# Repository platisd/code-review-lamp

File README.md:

# Code Review Lamp
A colorful lamp to notify the developer team for pending code reviews.

## What?
Code Review Lamp is a Neopixel-based, WiFi-enabled gadget that reminds developers to peer-review their colleagues' code. For each submission that has not been reviewed enough, it dims up and down at a color that is specific to the developer who is trying to introduce a new functionality to a project. The lamp stops shining once the code has either received enough reviews by the team, been merged or designated as *Work In Progress*. Currently, it is configured to work with [Gerrit](https://www.gerritcodereview.com/) (v.2.15) or GitHub, but it could be programmed to fetch data from different tools such as Jenkins, GitLab etc.

The gadget is comprised of an [ESP8266 microcontroller module](https://wiki.wemos.cc/products:d1:d1_mini) that connects wirelessly to the internet, as well as a [Neopixel ring](https://www.adafruit.com/product/1463) which displays various colors.

## Why?
At work, we are a fast-paced team that likes to commit (relatively) small and often. Every commit does not only have to pass the various tests that are being run by our Continuous Integration machinery, but also gets extensively code reviewed before allowed to be merged. Since we are *six* in total and our internal code of conduct dictates *two* positive approvals for each new submission, the lack of responsiveness when it comes to reviewing, can impede the development process and speed.

In an ideal world, developers would check their notification emails and would proceed on with reviewing their peer's code. However, as they are too absorbed by their ongoing work and perhaps slightly overwhelmed by the amount of emails they receive, these emails tend to be ignored. The common thought is that someone else in the team is going to review the code, but often no one does.

We have employed two different techniques so far to solve the problem. The first one includes shouting **CODE REVIEW** loudly and the second placing color-coded bean bags (I am not kidding :laughing:) on each others' desks. The third that hopes to rule them all is the Code Review Lamp!

Its advantage is that it continuously, and discretely, reminds developers that **the team** needs to review code and thus someone's work is being blocked as long as the lamp is shining. Additionally, they can see who is requesting the code review and how many reviews need to be conducted.

## How?
Reaping the benefits of the Code Review Lamp is simple for the development team member. They merely need to push code to Gerrit, add the group which includes all team members to the review and set the review to *Work in Progress* or *Ready for review* depending on whether they want the team to start or stop reviewing the code.

We have included a special user in our team's Gerrit group, representing the lamp, which is added along the team to each review. This user is being utilized by an ESP8266 microcontroller which connects to WiFi and [queries](https://gerrit-review.googlesource.com/Documentation/rest-api-changes.html) Gerrit for open reviews where this "lamp user" is a reviewer. Of course, it is not necessary to have a separate user for the lamp. Any team member's already existing account can be used and this way Code Review Lamps can be personalized. However, since we consider code reviews a *team activity* and the foundation of cross-functionality and knowledge-sharing, we have opted for the "team approach".

Next, for each review the user is assigned to, we determine how many reviews have been conducted and if they fall short of our agreed threshold, a color that corresponds to the *owner* of the review is displayed on the Neopixel ring.

### Software
The [Gerrit firmware](https://github.com/platisd/code-review-lamp/blob/master/firmware/gerrit_watcher/gerrit_watcher.ino), compatible with ESP8266 microcontrollers, utilizes the [Adafruit Neopixel](https://github.com/adafruit/Adafruit_NeoPixel) library to control the Neopixel ring. When using **Gerrit**, the JSON response is parsed manually, as existing solutions which would nicely serialize the whole stream would frequently cause heap overflow.

The [GitHub firmware](https://github.com/platisd/code-review-lamp/blob/master/firmware/github_watcher/github_watcher.ino) on the other hand does not parse the JSON response coming from **GitHub** itself directly. This is due to the API response being overly verbose for the ESP8266 microcontroller, which renders parsing it on the microcontroller infeasible. Instead, an external server has to be used which will process the data and merely send what colors should be displayed. An example of such a server, written in Python3, can be found [here](https://github.com/platisd/code-review-lamp/blob/master/firmware/github_watcher/github_reviews_watcher.py).

### Hardware
The gadget is rather simple to source and assemble. The only "custom" part is the [PCB](https://github.com/platisd/code-review-lamp/tree/master/hardware/gerrit_lamp) which merely connects the ESP8266 module with the Neopixel ring.

### Get started
After you have assembled the hardware, flash the firmware by following the steps below:
* If on Windows or Mac, download the [Serial to USB chip drivers](https://wiki.wemos.cc/downloads)
* Download and install the latest [Arduino IDE](https://www.arduino.cc/en/Main/Software) for your distribution
* Install the `Adafruit Neopixel` library
  * In Arduino IDE, click on `Sketch` :arrow_right: `Include Library` :arrow_right: `Manage Libraries`
  * Look for `Adafruit NeoPixel` and install the `Adafruit NeoPixel by adafruit`
* Install the ESP8266 SDK
  * In Arduino IDE, click on `File` :arrow_right: `Preferences` :arrow_right: `Additional Board Manager URLs`
  * Paste `http://arduino.esp8266.com/stable/package_esp8266com_index.json` and click `OK`
  * In Arduino IDE, click on `Tools` :arrow_right: `Board` :arrow_right: `Boards Manager`
  * Look for `esp8266` and install the `esp8266 by ESP8266 Community`
* Select the Wemos D1 Mini board
  * In Arduino IDE, click on `Tools` :arrow_right: `Board` :arrow_right: `LOLIN(WEMOS) D1 R2 & mini`
* Select the serial port your Code Review Lamp is connected to
  * In Arduino IDE, click on `Tools` :arrow_right: `Port`
* Copy & paste the [code](https://github.com/platisd/code-review-lamp/blob/master/firmware/gerrit_watcher/gerrit_watcher.ino) to your IDE
* Make the necessary adjustments for your own SSID, username etc
  * GitHub Token
    * Create a [personal access token](https://github.com/settings/tokens)
    * Give it all `repo` permissions if you want it to access your private repositories too, otherwise just `public_repo`
* Upload the firmware by clicking `Upload` (the right arrow button on the upper left corner of your IDE)

### How to use
* Commit your change to Gerrit or GitHub
* Add the group which includes the team as reviewers
  * A special "notification" user that will trigger the lamp should be part of the group
* ???
* Get your code reviewed faster!

## Components
* [Code Review Lamp PCB](https://www.pcbway.com/project/shareproject/W17435BSW42_code_review_lamp.html)
* [3D printed case](https://www.tinkercad.com/things/evNud1d8GYI)
* [16 RGB LED Neopixel Ring](https://www.adafruit.com/product/1463)
* [Wemos D1 Mini](https://wiki.wemos.cc/products:d1:d1_mini)
* 330Ohm resistor
* 470uF/16V capacitor
* M3x40mm screws (4)
* M3 nuts (4)
* Micro USB cable

## Media
* Article on [platis.solutions](https://platis.solutions/blog/2018/09/26/code-review-lamp/)
* [Demo video](https://www.youtube.com/watch?v=TPO2nQkfprY)

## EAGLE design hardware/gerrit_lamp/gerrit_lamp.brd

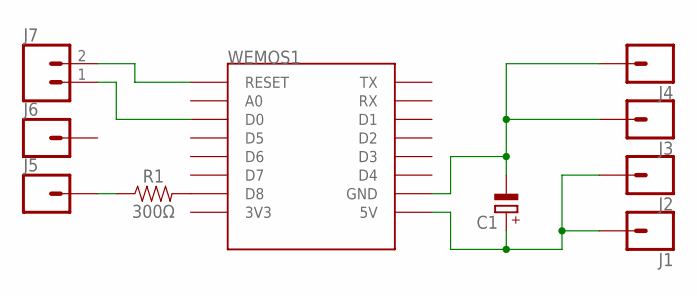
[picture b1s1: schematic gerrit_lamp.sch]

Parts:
C1: CPOL-EUE5-5; E5-5
J1, J2, J3, J4, J5, J6: CONN_01PTH_NO_SILK_KIT; 1X01NS_KIT
J7: CONN_02; 1X02
R1: 300Ω; AXIAL-0.3
WEMOS1: WEMOS-D1-MINI

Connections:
D0: J7.1, WEMOS1.D0
GND: C1.-, J3.1, J4.1, WEMOS1.GND
unnamed: R1.P$2 (2), WEMOS1.D8
unnamed: J5.1, R1.P$1 (1)
RST: J7.2, WEMOS1.RESET
VCC: C1.+, J1.1, J2.1, WEMOS1.5V

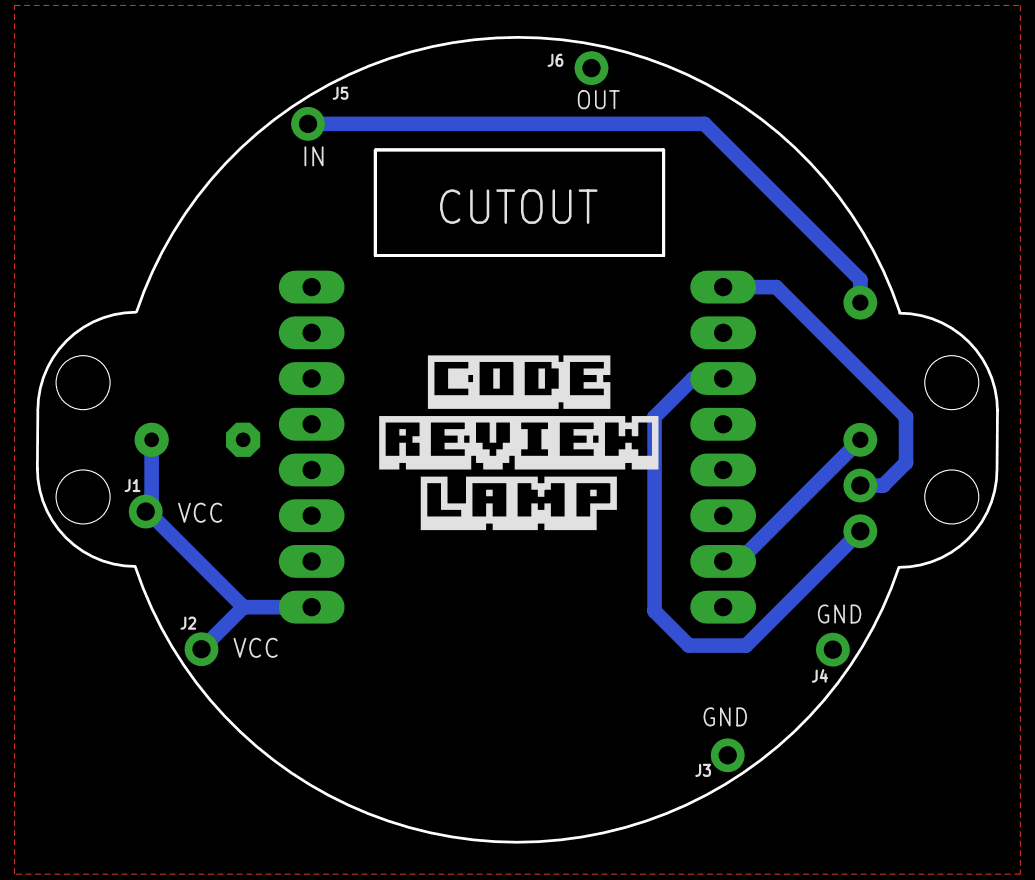
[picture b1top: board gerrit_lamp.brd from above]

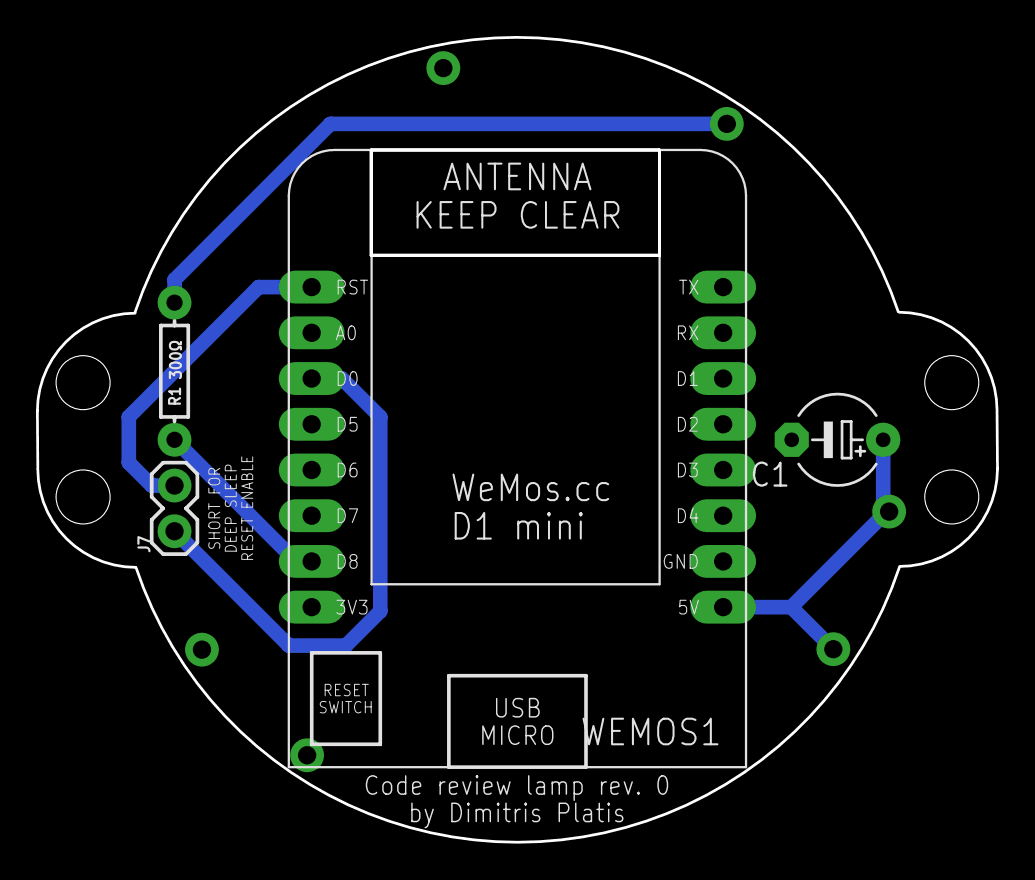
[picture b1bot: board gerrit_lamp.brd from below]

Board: 2 copper layers, 53.3 x 44.7 mm, 10 parts (4 on the bottom side), 6 nets.

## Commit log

2018-09-03 Add gitignore
2018-09-03 Add first version of gerrit watcher
2018-09-04 Use streams to parse JSON input
2018-09-04 Decrease heap memory usage
    Current setup has been tested with up to 7
    reviews. Serial is very shaky for some reason
    so using built in LED for debugging.
2018-09-08 Parse the stream directly without using ArduinoJSON
    Remove ArduinoJSON as the heap would often overflow in case there
    were too many JSON objects to handle. The new method does not
    completely rule out the problem (as vectors are used) but at least
    decreases a lot its likelihood.
2018-09-08 Retrieve owner id for reviews lacking approvals
2018-09-08 Add RGBColors
2018-09-09 Remove custom struct, use neopixel way instead
2018-09-09 Dim colors for each review using HSV format
2018-09-09 Move arduino sketch into its own folder
2018-09-09 Add license
2018-09-10 Optionally include a non-version controlled header
    The credentials.h file should include non-versioned controlled
    information such as passwords, gerrit server url's etc.
2018-09-10 Update gerrit IDs
2018-09-10 Add rev.0 hardware
2018-09-10 Move sketch into firmware folder
2018-09-18 Increase amount of enough code reviews
2018-09-18 Change user colors
    These were the commonly decided colors so we should abide by them
2018-09-18 Place review check logic into main loop
2018-09-19 Fix enough conducted reviews amount
2018-09-20 Improve overall behavior
    * Reduce logging
    * Reduce operation interval time
    * Other small fixes and improvements
2018-09-20 Make colors brighter
2018-09-20 Do not remove user when enough reviews are conducted
    * Instead of removing the user once enough reviews have been
    completed (which would require the owner to re-add the user
    once a new patchset has been introduced) we rely on the owner
    toggling the "WorkInProgress" option which would make the change
    'invisible' to our user.
    * Remove blocking error indication
2018-09-20 Replace map with switch-case
    For less heap memory consumption
2018-09-20 Print return characters when using printf
    For better presentations in serial shells other than the
    Serial Monitor of Arduino IDE.
2018-09-20 Removed unused function
2018-09-20 Remove excess whitespaces
2018-09-23 Improve code presentation
    * Remove magic numbers
    * Add method description
    * Turn more variables to auto
2018-09-23 Add README
2018-09-24 Update main picture
2018-09-25 Add instruction on how to get started
2018-09-25 Add media links
2018-09-26 Avoid pushing an empty owner id in case of GET error
2018-09-26 Correct team size
    We are technically 6, but two members are 50%
    :stuck_out_tongue_closed_eyes:
2018-09-26 Add usage instructions
2018-09-26 Avoid undefined behavior of front() in possibly empty container
2018-09-27 Add missing step
    Arduino IDE by default does not include the ESP8266 boards
2018-10-04 Adding skins for geerit lamp: Pulse and Radar
2018-10-11 Adding skins for gerrit lamp: Pulse and Radar
2018-10-12 Added cool radar effect
2018-10-12 Moving startingPixel out of global scope
2018-10-12 Bug: Removed duplicated lines
2018-10-15 Adding skins for gerrit lamp: Pulse and Radar
    * Adding skins for geerit lamp: Pulse and Radar
    * Adding skins for gerrit lamp: Pulse and Radar
    * Added cool radar effect
    * Moving startingPixel out of global scope
    * Bug: Removed duplicated lines
2018-10-18 Fix sketch aesthetics
    * Fix indentations
    * Fix unnecessary ussage of unsigned int
2019-04-10 Add GitHub watcher
2019-04-12 Update documentation to include GitHub
2020-03-21 Add corona lamp
2020-03-21 Document corona lamp
2020-03-21 Remove unused colors
2020-03-23 Add corona lamp photo & personalization instructions

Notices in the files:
parts and their libraries:
SparkFun-Resistors: Licensing: Creative Commons ShareAlike 4.0 International - https://creativecommons.org/licenses/by-sa/4.0
